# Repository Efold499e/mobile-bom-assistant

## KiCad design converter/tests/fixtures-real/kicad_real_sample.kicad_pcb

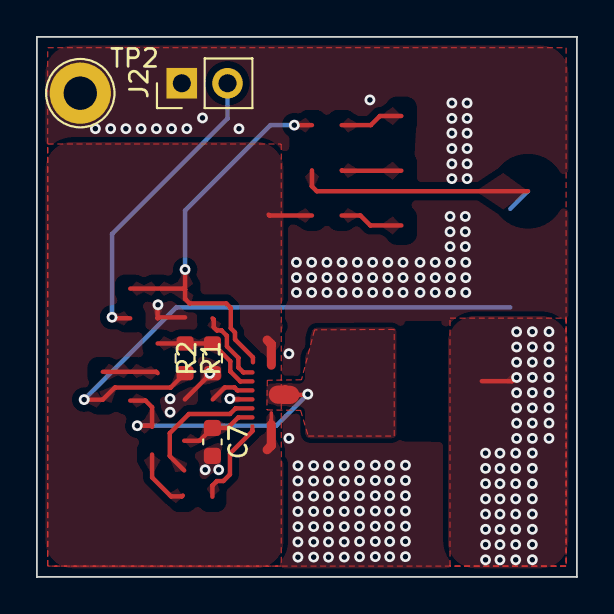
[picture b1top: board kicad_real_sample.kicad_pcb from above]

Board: 2 copper layers, 30.0 x 30.0 mm, 5 parts (0 on the bottom side), 2 nets.

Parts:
C7: 1uF; C_0603_1608Metric
J2: PWM IN; PinHeader_1x02_P2.54mm_Vertical
R1: 28.7k; R_0603_1608Metric
R2: 20k; R_0603_1608Metric
TP2: TestPoint; TestPoint_Loop_D2.50mm_Drill1.85mm

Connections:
GND: C7.2, J2.1, R2.1, TP2.1 (1_1)
unnamed: R1.1, R2.2
